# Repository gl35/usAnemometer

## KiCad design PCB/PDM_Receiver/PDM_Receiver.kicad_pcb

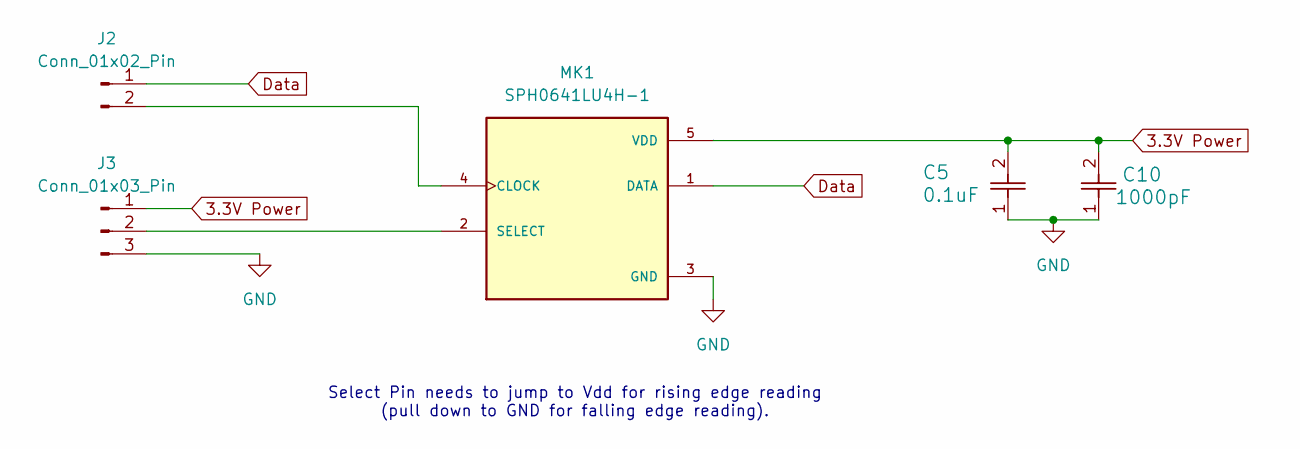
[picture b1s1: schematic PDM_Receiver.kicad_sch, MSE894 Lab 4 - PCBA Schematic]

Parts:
C5: 0.1uF; C_0805_2012Metric
C10: 1000pF; C_0805_2012Metric
J2: Conn_01x02_Pin; PinHeader_1x02_P2.54mm_Vertical
J3: Conn_01x03_Pin; PinHeader_1x03_P2.54mm_Vertical
MK1: SPH0641LU4H-1; MIC_SPH0641LU4H-1; DIGI-KEY_PART_NUMBER 423-1402-1-ND

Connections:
3.3V Power: C5.2, C10.2, J3.1, MK1.5 (VDD)
Data: J2.1, MK1.1 (DATA)
GND: C5.1, C10.1, J3.3, MK1.3 (GND)
unnamed: J2.2, MK1.4 (CLOCK)
unnamed: J3.2, MK1.2 (SELECT)

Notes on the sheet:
Select Pin needs to jump to Vdd for rising edge reading (pull down to GND for falling edge reading).

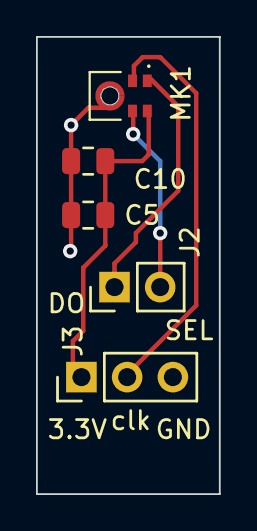
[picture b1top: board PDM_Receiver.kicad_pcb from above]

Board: 4 copper layers, 10.2 x 25.4 mm, 5 parts (0 on the bottom side), 5 nets.

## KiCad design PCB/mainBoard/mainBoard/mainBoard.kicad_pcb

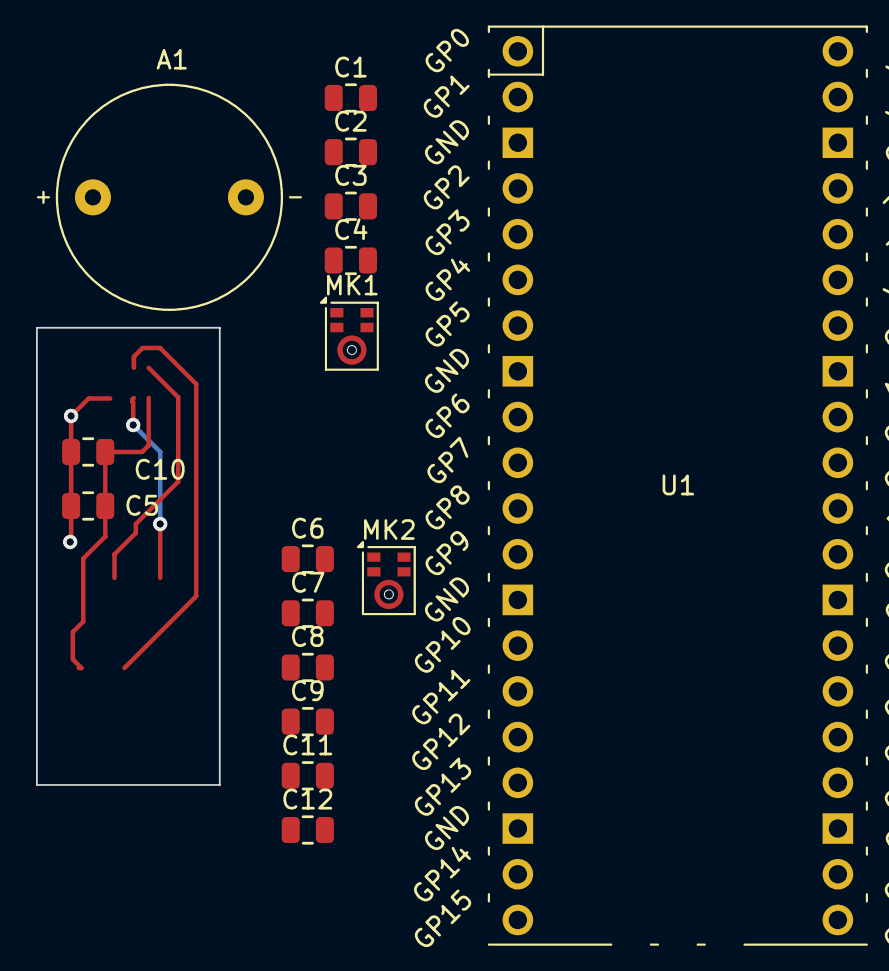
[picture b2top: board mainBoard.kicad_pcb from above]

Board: 4 copper layers, 16 parts (0 on the bottom side), 7 nets.

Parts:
A1: CUSA-T75-18-2400-TH; XDCR_CUSA-T75-18-2400-TH
C1, C3, C5, C6, C8, C11: 0.1uF; C_0805_2012Metric
C2, C4, C7, C9, C10, C12: 1000pF; C_0805_2012Metric
MK1, MK2: SPH0641LU4H-1; Knowles_LGA-5_3.5x2.65mm
U1: Pico W

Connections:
3.3V: C6.2, C7.2, C8.2, C9.2, MK1.2 (SEL), MK1.5 (VDD), MK2.2 (SEL), MK2.5 (VDD), U1.36 (3V3)
3.072Mhz clock: MK1.4 (CLOCK), MK2.4 (CLOCK), U1.21 (GPIO16)
39kHz: C1.2, C2.2, U1.1 (GPIO0)
GND: C1.1, C2.1, C3.1, C4.1, C5.1, C6.1, C7.1, C8.1, C9.1, C10.1, C11.1, C12.1, MK1.3 (GND), MK2.3 (GND), U1.3 (GND)
PDM1: C11.2, C12.2, MK1.1 (DATA), U1.25 (GPIO19)
PDM2: C5.2, C10.2, MK2.1 (DATA), U1.24 (GPIO18)
Vbus: C3.2, C4.2

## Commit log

2024-06-03 added state machine
2024-06-17 backup
2024-08-17 new commit
2025-08-11 addedPCBA
